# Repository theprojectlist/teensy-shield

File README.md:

# teensy-shield

A bridge shield between a Teensy 4.0 I²C bus and LVDS transcoder. This shield enables symmetric long-distance and dynamic peripheral control over a regular I²C connection.

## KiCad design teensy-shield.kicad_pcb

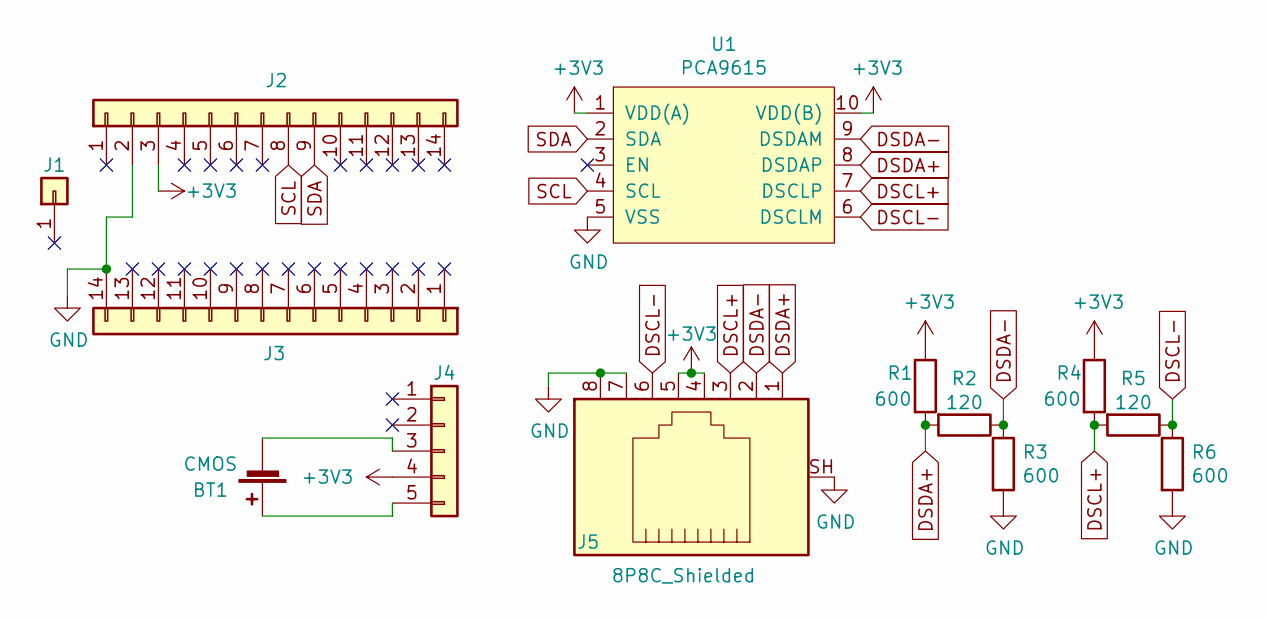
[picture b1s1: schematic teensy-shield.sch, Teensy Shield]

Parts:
BT1: CMOS; BatteryHolder_Seiko_MS621F
J1: Conn_01x01; PinSocket_1x01_P2.54mm_Vertical
J2, J3: Conn_01x14; PinSocket_1x14_P2.54mm_Vertical
J4: Conn_01x05; PinSocket_1x05_P2.54mm_Vertical
J5: 8P8C_Shielded; RJ45_Amphenol_RJHSE5380
R1, R3, R4, R6: 600; R_0603_1608Metric_Pad1.05x0.95mm_HandSolder
R2, R5: 120; R_0603_1608Metric_Pad1.05x0.95mm_HandSolder
U1: PCA9615; TSSOP-10_3x3mm_P0.5mm

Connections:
+3V3: J2.3, J4.4, J5.4, J5.5, R1.1, R4.1, U1.1 (VDD(A)), U1.10 (VDD(B))
DSCL+: J5.3, R4.2, R5.2, U1.7 (DSCLP)
DSCL-: J5.6, R5.1, R6.1, U1.6 (DSCLM)
DSDA+: J5.1, R1.2, R2.2, U1.8 (DSDAP)
DSDA-: J5.2, R2.1, R3.1, U1.9 (DSDAM)
GND: J2.2, J3.14, J5.7, J5.8, J5.SH, R3.2, R6.2, U1.5 (VSS)
unnamed: BT1.1 (+), J4.5
unnamed: BT1.2 (-), J4.3
SCL: J2.8, U1.4 (SCL)
SDA: J2.9, U1.2 (SDA)

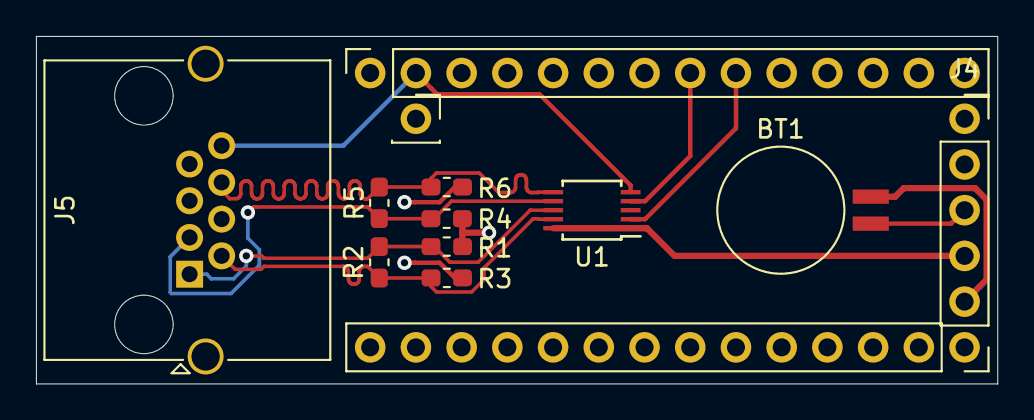
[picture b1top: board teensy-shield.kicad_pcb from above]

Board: 4 copper layers, 53.4 x 19.3 mm, 13 parts (0 on the bottom side), 10 nets.

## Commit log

2020-02-05 Add Teensy 4 shield
